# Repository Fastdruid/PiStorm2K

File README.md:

# PiStorm2K v2.1 - BOSS Edition.

This is a rework of the original PiStorm2K to add some additional potential capabilities while remaining 100% compatible with existing and future firmware. 

The original PiStorm2K was imported from Gerbers into KiCAD and then revised. The initial KiCAD PiStorm2K is also contained within this repo however there were a lots of bits cleaned-up on v2.0 that didn't happen on v1.0. 

# Why

An excellent question. I don't even have an Amiga 2000 (any donations of one welcome however!)
This all spiralled from LazaruStorm not playing nicely with the original Processor on my 68k. This took me down the hole of *why* it didn't, because it _should_. In short the issue is due to the E(nable) Clock that is used for 6800 type devices (which the CIA chips are). The 68k does not stop generating the E-Clock, there is no way to tell at what state it will start up in and so it's a random lottery if the E-Clock generated from the PiStorm happens to "line up". 

I then took a look at the Verilog firmware and thought "this appears reasonably understandable". From there I got the PiStorm to start off by listening for the E-Clock, and either generate one or sync to an existing one. After that I got it to correctly Bus Arbitrate and request the Bus rather than the brute force method LazaruStorm uses of just holding BR asserted. 

Once I'd got that working nicely I then got it to swap between PiStorm and original processor using a long hold Ctrl-A-A. 

At the same time I looked at the Zorro-II specs pinout for the Denise I'd just built and realised it was 98% compatible with the A2000 Co-Processor, had no 7MHz clock on pin 7 but could do the same as the A2000 and generate it from C1/C3.
I ordered one of those and created an adaptor to fit it into the Zorro-II slot and re-wrote the firmware to swap between modes on the CLK_SEL pin (because Denise can't do a long Ctrl-A-A but has a mechanism to disable items via numlock->reset).

I also designed an adaptor to fit the card inside the A500(+). By this stage I was experimenting with a bunch of stuff and wanted something where I could access the remaining lines on the CPLD and at the same time be a useful upgrade. Which is where this comes in.
With appropriate firmware it should be able to do the same in a B2000 as it does in the A500(+) and Denise. ie swap between 68k and PiStorm at will. In theory the firmware may also do DMA...but that is very, very untested. 

# Status
V2.0 not recommended for production. 
V2.1 Fixed issues with v2.0

# Building 
## Options
   1) U6 & C13 are optional. Not so much use on the A2000, desired for the B2000
   2) H1, H2 and H3 are optional as they can be controlled by solder blobs however H4 is required. 
   3) R3 is optional and for 99.9% of use cases is pointless. 
   4) For A2000 R4 can be omitted. 

## Known issues
 1) V2.0 of the BOM incorrectly used 0603 for the resistors and capacitors where the footprint was 0402. Fixed in BOM v2.0.1
 2) V2.0 of the BOM incorrectly used a 680R resistor instead of a 68R for R3. Fixed in BOM v2.0.1
 3) V2.0 of the BOM incorrectly used a 1K1 resistor instead of a 1K for R3. Fixed in BOM v2.0.1
 4) Rotations of the chips are all wrong from the placement file. I need to understand here why KiCAD messed it up but if ordering from JLCPCB you will need to manually rotate them to the correct orientation.
 5) V2.0 Rogue via missed in DRC shorts 5v to GND. Can be drilled out but will be fixed in V2.1

# Summary of changes
### Additional control lines.

INT2 => Pin 87  
CFGOUTn => Pin 92  
INT6 => Pin 1  
XRDY => Pin 95  
OVR => Pin 11  

### Additional Headers / Jumpers

INT PWR => INTernal PoWeR - Optional to power the RPi from the board or use a seperate Power Supply.   
EXT => Extra - For future expansion  
E RES => This is a bit of a specialist one, this edition can be used in a normal Zorro slot with some modifications. Depending on board you may need to add a 68R resistor to the E-Clock. This jumper **BYPASSES** it. A/B2000 users should either have a jumper or solder the blob.   
CLK SEL => CLocK SELect - Close to use C1/C3 for the clock. Note that the 7MHz clock is *ALWAYS* recommended over the C1/C3 if you have it.   
BJ => Pull down BOSS (pin 20) to GND to take over from the onboard processor.   
JTAG => TDI, TCK, TMS, TDO header (see section on JTAG).   
PWR => +5V, GND, VCC_INT and VCC. Normally VCC and VCC_INT will be identical at 3.3v however if MAX V is used with the second 1.8v regulator VCC_INT will be 1.8v.   
IPL2-0 => IPL2, IPL1, IPL0. - Another specialist one. (see "use in Zorro-II slots")  

### Solder blob jumpers

SJ1 - Close to use C1/C3 - semi-permanent version of **CLK SEL** Jumper. A2000 users should close this. B2000 should leave it open.   
SJ2 - Close to bypass 68R on E-Clock - semi-permanent version of **E RES** Jumper. A2000 and B2000 users should close this.  
BOSS - Close to pull BOSS down to GND - semi-permanent version of BOSS Jumper.  
D-BOSS - Cut to disable pin 20 (see "use in Zorro slot").  
TDI => Cut pin 1-2 to disable TDI to the CPLD. Close 2-3 to redirect RPi Pin 13 (GPIO27) to Pin 89 on the CPLD.  
TMS => Cut pin 1-2 to disable TMS to the CPLD. Close 2-3 to redirect RPi Pin 18 (GPIO24) to Pin 91 on the CPLD.  
TDO => Cut pin 1-2 to disable TDO to the CPLD. Close 2-3 to redirect RPi Pin 22 (GPIO25) to Pin 85 on the CPLD.  
TCK => Cut pin 1-2 to disable TCK to the CPLD. Close 2-3 to redirect RPi Pin 37 (GPIO26) to Pin 86 on the CPLD.  
7MHz => Cut to disconnect pin 7 (see "use in Zorro-II slots").  

### Extra pins
The remaining 4 extra pins are brought out to solder pads.   
P78 - Pin 78 CPLD  
P81 - Pin 81 CPLD  
P82 - Pin 82 CPLD  
P83 - Pin 83 CPLD  

# Use in Zorro-II slots. 

This can be used in an unbuffered Zorro-II slot noting a couple of potential issues.  

1) Zorro is a 100 pin slot, the Co-Processor is 86. It *must* be fitted so pin 1 is at pin 1. That means that there should be a space at the "front" of the Amiga. 
2) Pin 20 on Zorro-II is -12v. If you plug this straight in you will fry the CPLD. Cut the D-BOSS solder jumper and ensure there is no continuity across it.
3) There is no clock on pin 7. Depending on Zorro implementation this may be /OWN. If this is the case then it can be disconnected by cutting the solder blob link marked 7MHz.
4) Depending on Zorro implentation there may be no IPL0-2 lines. These are essential and therefore a header is supplied.
5) Depending on Zorro implementation there may or may not be a 68R between the Zorro slot and the CIA chips. This probably isn't a *massive* issue (after all the early A500's didn't) but a jumper is supplied just in case.

# JTAG programming.

The original PiStorm uses 4 pins from the Pi to allow quick and easy reprogramming of the CPLD. This has numerous advantages however it leaves 4 GPIO pins "off the table" that could be used. Nothing *currently* uses them however the PiStorm32 uses pins 13, 18, 22 and 37 connected to pins 31, 28,  4 &  33 which are used as PI_A[0], PI_A[1], PI_WR and PI_SER_CLK.
In theory these could be used however it makes programming a manual job to connect up a programmer. To make it slightly easier there is a 4-pin header which have the 4 pins required to flash the CPLD from the Pi using the normal procedure. 

If you wish to program the CPLD via this method use the following pinout to connect the Pi to the JTAG connector as follows.

<IMG SRC="https://www.raspberrypi.com/documentation/computers/images/GPIO-Pinout-Diagram-2.png">

Pin 13 on the Pi to TDI  (Pin 1, top of the board)  
Pin 37 on the Pi to TCK  (Pin 2)  
Pin 18 on the Pi to TMS  (Pin 3)  
Pin 22 on the Pi to TDO  (Pin 4)  

You will also need to connect power and ground to the Pi. To aid in this there is a second header next to the JTAG header marked PWR, connect power as follows.
Pin 1 or 2 on the Pi to +5V (Pin 1, top of the board).  
Pin 6,9,14,20,25,30,34 or 39 on the Pi to GND (Pin 2).  

I strongly recommend that you connect these with power off! You can then turn on your Amiga (ensuring the Pi cannot short on anything) which will boot the Pi and then allow you to flash as normal. 

Alternatively you can remove the PiStorm2k from the Amiga and provide power to the Pi via the USB power connector. This will then provide enough power back to the PiStorm2K to flash. 

# New Firmware!

This is the juicy part. There is new exciting firmware which attempts both to properly negotiate BOSS and maybe even allow Bus Arbitration which will (maybe) allow DMA. See the firmware folder for further details (if there isn't one then nothing is yet released).

# DISCLAIMER / LICENSE

Both the original PiStorm and this modification fall under the MIT License. 

THIS DESIGN, ANY HARDWARE PRODUCED FROM IT, ANY FIRMWARE OR SOFTWARE IS PROVIDED "AS IS" WITHOUT WARRANTY OF ANY KIND, EXPRESS OR IMPLIED, INCLUDING BUT NOT LIMITED TO THE WARRANTIES OF MERCHANTABILITY, FITNESS FOR A PARTICULAR PURPOSE AND NONINFRINGEMENT. IN NO EVENT SHALL THE AUTHORS OR COPYRIGHT HOLDERS BE LIABLE FOR ANY CLAIM, DAMAGES OR OTHER LIABILITY, WHETHER IN AN ACTION OF CONTRACT, TORT OR OTHERWISE, ARISING FROM, OUT OF OR IN CONNECTION WITH THE DESIGN, SOFTWARE, HARDWARE, FIRMWARE OR THE USE OR OTHER DEALINGS IN THE DESIGN, SOFTWARE, HARDWARE or FIRMWARE.

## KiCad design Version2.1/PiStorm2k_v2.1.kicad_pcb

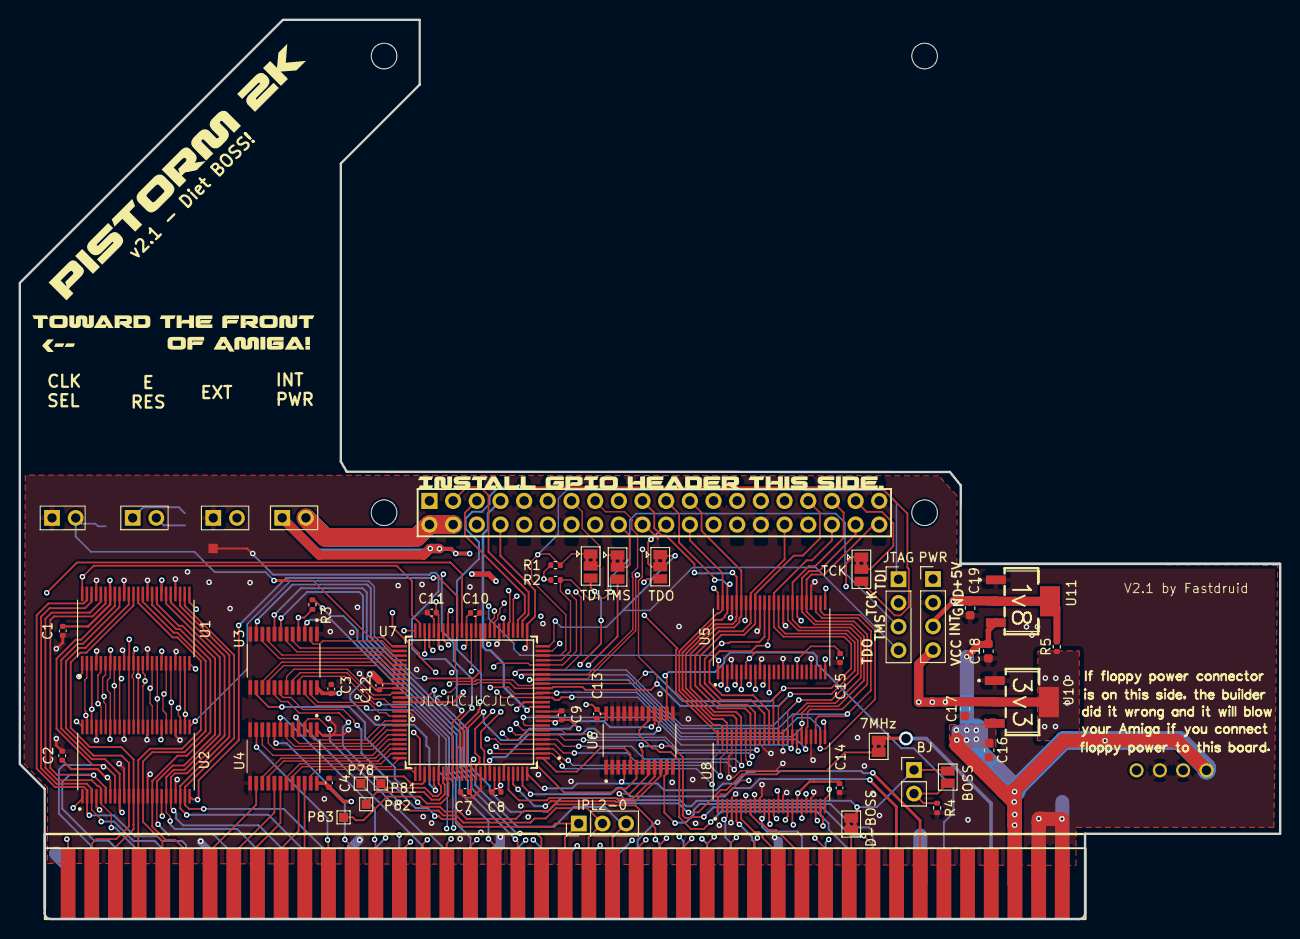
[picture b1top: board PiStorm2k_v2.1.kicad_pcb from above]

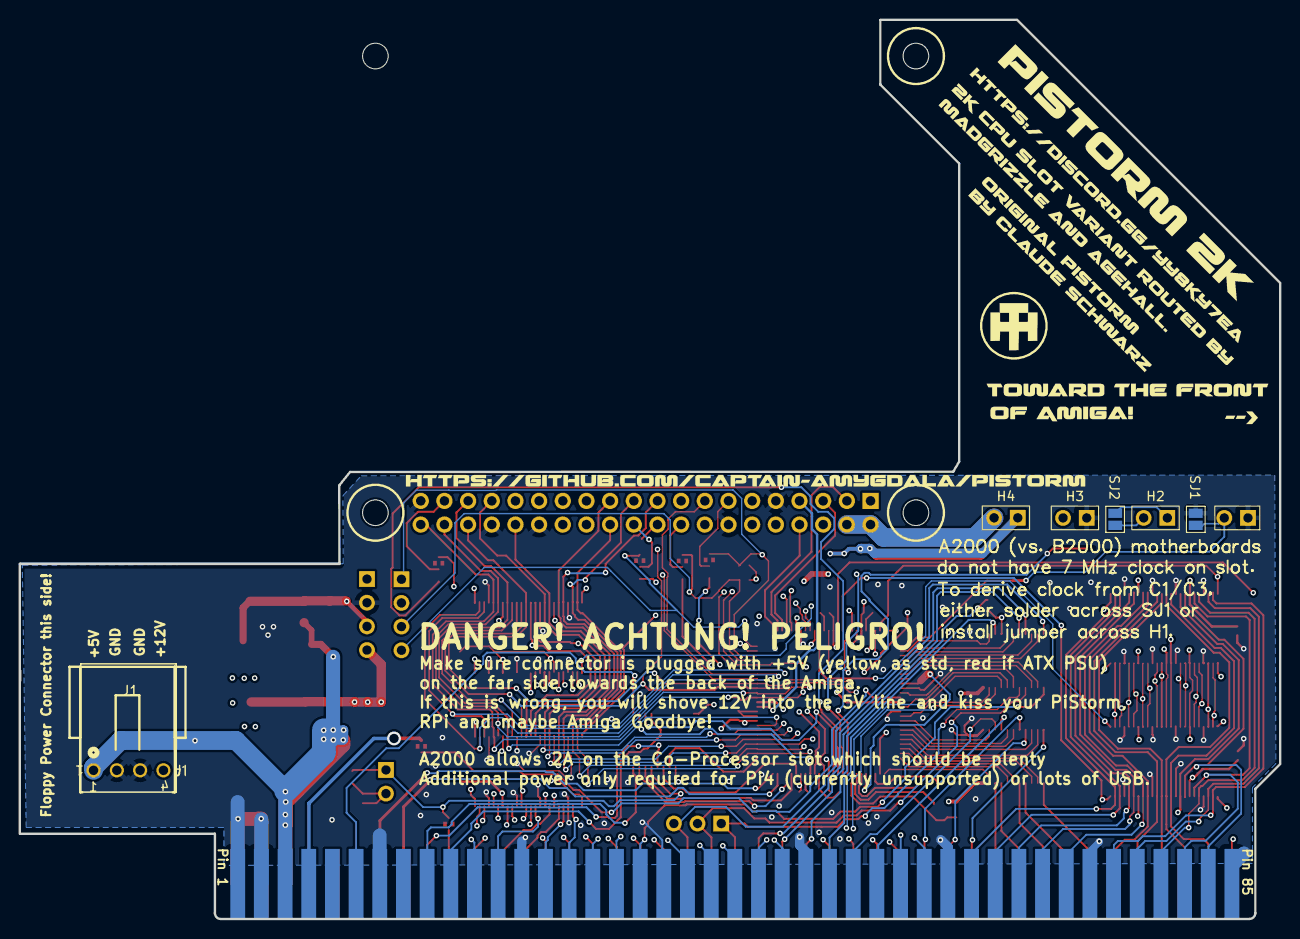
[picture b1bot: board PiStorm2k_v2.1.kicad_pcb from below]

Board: 4 copper layers, 135.2 x 96.5 mm, 56 parts (3 on the bottom side), 158 nets.

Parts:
7MHz: SolderJumper-2_P1.3mm_Bridged2Bar_Pad1.0x1.5mm
BJ: PinHeader_1x02_P2.54mm_Vertical
BOSS: SolderJumper-2_P1.3mm_Open_Pad1.0x1.5mm
C1, C2, C3, C4, C7, C8, C9, C10, C11, C12, C13, C14, C15: 100nf; C_0402_1005Metric
C16, C17, C18, C19: C_0603_1608Metric
D-BOSS: SolderJumper-2_P1.3mm_Bridged2Bar_Pad1.0x1.5mm
H1, H2, H3, H4: PinHeader_1x02_P2.54mm_Horizontal
IPL2-0: PinHeader_1x03_P2.54mm_Vertical
J1: CONN_171826-4_TYCO_TYC
JTAG: PinHeader_1x04_P2.54mm_Vertical
P78, P81, P82, P83: TestPoint_Pad_1.0x1.0mm
PWR: PinHeader_1x04_P2.54mm_Vertical
R1, R2, R3, R4, R5: R_0402_1005Metric
RPi: Raspberry_Pi_2_3; raspberrypi_2_3
SJ1, SJ2: SolderJumper-2_P1.3mm_Open_Pad1.0x1.5mm
TCK: SolderJumper-3_P1.3mm_Bridged2Bar12_Pad1.0x1.5mm
TDI: SolderJumper-3_P1.3mm_Bridged2Bar12_Pad1.0x1.5mm
TDO: SolderJumper-3_P1.3mm_Bridged2Bar12_Pad1.0x1.5mm
TMS: SolderJumper-3_P1.3mm_Bridged2Bar12_Pad1.0x1.5mm
U1, U2, U5, U8: SN74LVC16374DGGR; SOP50P810X120-48N
U3, U4, U6: SN74CBTD3384PWR; SOP65P640X120-24N
U7: QFP50P1600X1600X120-100N
U10, U11: VREG_LM1117IMPX-3.3
Zorro II / A(B) Co-Processor: zorro2port; A500_Edge

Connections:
1_CPLD: U6.5, U7.1
4_E: H2.1, R3.1, SJ2.2, U3.4
52_1B1: U3.2, U7.52
53_1B2: U3.5, U7.53
54_1B3: U3.6, U7.54
55_1B4: U3.9, U7.55
56_1B5: U3.10, U7.56
57_2B1: U3.15, U7.57
58_2B2: U3.16, U7.58
61_2B3: U3.19, U7.61
62_GCLK2: 7MHz.1, U7.62
64_2B4: U3.20, U7.64
66_2B5: U3.23, U7.66
67_1B1: U4.2, U7.67
68_1B2: U4.5, U7.68
69_1B1: U4.6, U7.69
70_1B4: U4.9, U7.70
71_1B5: U4.10, U7.71
72_2B1: U4.15, U7.72
73_2B2: U4.16, U7.73
74_2B3: U4.19, U7.74
75_2B4: U4.20, U7.75
76_2B5: U4.23, U7.76
78_CPLD: P78.1, U7.78
81_CPLD: P81.1, U7.81
82_CPLD: P82.1, U7.82
83_CPLD: P83.1, U7.83
85_CPLD: TDO.3, U7.85
86_CPLD: TCK.3, U7.86
87_CPLD: U6.16, U7.87
89_CPLD: TDI.3, U7.89
91_CPLD: TMS.3, U7.91
92_CPLD: U6.15, U7.92
95_1B3: U6.6, U7.95
96_1B4: U6.9, U7.96
97_1B5: U6.10, U7.97
+3.3V: RPi.1, RPi.17
+5V: C3.2, C4.1, C13.2, C16.1, C18.2, H4.1, J1.1, PWR.1, U3.24, U4.24, U6.24, U10.3, U11.3, Zorro II / A(B) Co-Processor.5, Zorro II / A(B) Co-Processor.6
+12V: J1.4, Zorro II / A(B) Co-Processor.10
A1: U8.3, Zorro II / A(B) Co-Processor.29
A2: U8.5, Zorro II / A(B) Co-Processor.27
A3: U8.6, Zorro II / A(B) Co-Processor.26
A4: U8.8, Zorro II / A(B) Co-Processor.24
A5: U8.9, Zorro II / A(B) Co-Processor.21
A6: U8.11, Zorro II / A(B) Co-Processor.23
A7: U8.12, Zorro II / A(B) Co-Processor.28
A8: U8.13, Zorro II / A(B) Co-Processor.30
A9: U8.14, Zorro II / A(B) Co-Processor.32
A10: U8.16, Zorro II / A(B) Co-Processor.34
A11: U8.17, Zorro II / A(B) Co-Processor.36
A12: U8.19, Zorro II / A(B) Co-Processor.38
A13: U8.20, Zorro II / A(B) Co-Processor.39
A14: U8.22, Zorro II / A(B) Co-Processor.41
A15: U8.23, Zorro II / A(B) Co-Processor.43
A16: U5.2, Zorro II / A(B) Co-Processor.45
A17: U5.3, Zorro II / A(B) Co-Processor.47
A18: U5.5, Zorro II / A(B) Co-Processor.52
A19: U5.6, Zorro II / A(B) Co-Processor.54
A20: U5.8, Zorro II / A(B) Co-Processor.56
A21: U5.9, Zorro II / A(B) Co-Processor.58
A22: U5.11, Zorro II / A(B) Co-Processor.57
A23: U5.12, Zorro II / A(B) Co-Processor.59
ADDR_LTCH_0: U7.44, U8.48
ADDR_LTCH_8: U7.42, U8.25
ADDR_LTCH_16: U5.48, U7.47
ADDR_LTCH_24: U5.25, U7.48
ADDR_OE: U5.1, U5.24, U7.43, U8.1, U8.24
AS: U4.14, Zorro II / A(B) Co-Processor.74
AUX0: RPi.27, U7.30
AUX1: RPi.28, U7.33
BEER: U3.8, Zorro II / A(B) Co-Processor.46
BGACK: U4.8, Zorro II / A(B) Co-Processor.62
BOSS: BJ.1, BOSS.2, D-BOSS.2, U6.8
BOSS_G: BJ.2, BOSS.1, R4.1
BOSS_PIN: D-BOSS.1, Zorro II / A(B) Co-Processor.20
CBG: U4.11, Zorro II / A(B) Co-Processor.64
CBR: U4.7, Zorro II / A(B) Co-Processor.60
CCK: U7.99, Zorro II / A(B) Co-Processor.16
CCKQ: U7.100, Zorro II / A(B) Co-Processor.14
CFGOUTn: U6.14, Zorro II / A(B) Co-Processor.11
CLK_SEL: H1.2, SJ1.1, U7.51
D0: U1.47, U2.2, Zorro II / A(B) Co-Processor.75
D1: U1.46, U2.3, Zorro II / A(B) Co-Processor.77
D2: U1.44, U2.5, Zorro II / A(B) Co-Processor.79
D3: U1.43, U2.6, Zorro II / A(B) Co-Processor.81
D4: U1.41, U2.8, Zorro II / A(B) Co-Processor.83
D5: U1.40, U2.9, Zorro II / A(B) Co-Processor.86
D6: U1.38, U2.11, Zorro II / A(B) Co-Processor.84
D7: U1.37, U2.12, Zorro II / A(B) Co-Processor.82
D8: U1.36, U2.13, Zorro II / A(B) Co-Processor.80
D9: U1.35, U2.14, Zorro II / A(B) Co-Processor.78
D10: U1.33, U2.16, Zorro II / A(B) Co-Processor.76
D11: U1.32, U2.17, Zorro II / A(B) Co-Processor.71
D12: U1.30, U2.19, Zorro II / A(B) Co-Processor.69
D13: U1.29, U2.20, Zorro II / A(B) Co-Processor.67
D14: U1.27, U2.22, Zorro II / A(B) Co-Processor.65
D15: U1.26, U2.23, Zorro II / A(B) Co-Processor.63
DATA_RD_LTCH_HB: U1.25, U7.50
DATA_RD_LTCH_LB: U1.48, U7.49
DATA_RD_OE: U1.1, U1.24, U7.38
DATA_WR_LTCH_HB: U2.25, U7.36
DATA_WR_LTCH_LB: U2.48, U7.40
DATA_WR_OE: U2.1, U2.24, U7.41
DTACK: U4.22, Zorro II / A(B) Co-Processor.66
E: H2.2, R3.2, SJ2.1, Zorro II / A(B) Co-Processor.50
EXTRA: H3.2, U7.77
FC0: U3.22, Zorro II / A(B) Co-Processor.31
FC1: U3.21, Zorro II / A(B) Co-Processor.33
FC2: U3.14, Zorro II / A(B) Co-Processor.35
GND: C1.1, C2.2, C4.2, C7.2, C8.1, C9.2, C10.2, C11.2, C12.2, C13.1, C14.2, C15.2, C16.2, C17.1, C18.1, C19.1, H1.1, H3.1, J1.2, J1.3, PWR.2, R4.2, RPi.6, RPi.9, RPi.14, RPi.20, RPi.25, RPi.30, RPi.34, RPi.39, SJ1.2, U1.4, U1.10, U1.15, U1.21, U1.28, U1.34, U1.39, U1.45, U2.4, U2.10, U2.15, U2.21, U2.28, U2.34, U2.39, U2.45, U3.1, U3.12, U3.13, U4.1, U4.12, U4.13, U5.4, U5.10, U5.15, U5.21, U5.28, U5.34, U5.39, U5.45, U6.1, U6.2, U6.3, U6.12, U6.13, U6.18, U6.19, U6.20, U6.21, U6.22, U6.23, U7.10, U7.11, U7.32, U7.37, U7.46, U7.60, U7.65, U7.79, U7.90, U7.93, U8.4, U8.10, U8.15, U8.21, U8.28, U8.34, U8.39, U8.45, U10.1, U11.1, Zorro II / A(B) Co-Processor.1, Zorro II / A(B) Co-Processor.2, Zorro II / A(B) Co-Processor.3, Zorro II / A(B) Co-Processor.4, Zorro II / A(B) Co-Processor.13, Zorro II / A(B) Co-Processor.25, Zorro II / A(B) Co-Processor.37, Zorro II / A(B) Co-Processor.49, Zorro II / A(B) Co-Processor.61, Zorro II / A(B) Co-Processor.73, Zorro II / A(B) Co-Processor.85
HLT: U4.4, Zorro II / A(B) Co-Processor.55
INT2: U6.17, Zorro II / A(B) Co-Processor.19
INT6: U6.4, Zorro II / A(B) Co-Processor.22
IPL0: IPL2-0.3, U3.11, Zorro II / A(B) Co-Processor.40
IPL1: IPL2-0.2, U3.17, Zorro II / A(B) Co-Processor.42
IPL2: IPL2-0.1, U3.18, Zorro II / A(B) Co-Processor.44
LDS: U4.18, Zorro II / A(B) Co-Processor.70
OVR: U6.11, Zorro II / A(B) Co-Processor.17
PICLK: RPi.7, U7.12
PI_+5V: H4.2, RPi.2, RPi.4
RST: U4.3, Zorro II / A(B) Co-Processor.53
R_W: U4.21, Zorro II / A(B) Co-Processor.68
SA0: RPi.29, U7.34
SA1: RPi.5, U7.28
SA2: RPi.3, U7.27
SD0: RPi.24, U1.2, U2.47, U5.47, U7.2, U8.47
SD1: RPi.21, U1.3, U2.46, U5.46, U7.3, U8.46
SD2: RPi.19, U1.5, U2.44, U5.44, U7.4, U8.44
SD3: RPi.23, U1.6, U2.43, U5.43, U7.5, U8.43
SD4: RPi.32, U1.8, U2.41, U5.41, U7.6, U8.41
SD5: RPi.33, U1.9, U2.40, U5.40, U7.7, U8.40
SD6: RPi.8, U1.11, U2.38, U5.38, U7.26, U8.38
SD7: RPi.10, U1.12, U2.37, U5.37, U7.21, U8.37
SD8: RPi.36, U1.13, U2.36, U5.36, U7.17, U8.36
SD9: RPi.11, U1.14, U2.35, U5.35, U7.16, U8.35
SD10: RPi.12, U1.16, U2.33, U5.33, U7.20, U8.33
SD11: RPi.35, U1.17, U2.32, U5.32, U7.8, U8.32
SD12: RPi.38, U1.19, U2.30, U5.30, U7.15, U8.30
SD13: RPi.40, U1.20, U2.29, U5.29, U7.14, U8.29
SD14: RPi.15, U1.22, U2.27, U5.27, U7.19, U8.27
SD15: RPi.16, U1.23, U2.26, U5.26, U7.18, U8.26
SOE: RPi.31, U7.35
SWE: RPi.26, U7.29
TCK: JTAG.2, TCK.1, U7.24
TCK_PIN: RPi.37, TCK.2
TDI: JTAG.1, R1.2, TDI.1, U7.23
TDI_PIN: RPi.13, TDI.2
TDO: JTAG.4, TDO.1, U7.25
TDO_PIN: RPi.22, TDO.2
TMS: JTAG.3, R2.2, TMS.1, U7.22
TMS_PIN: RPi.18, TMS.2
UDS: U4.17, Zorro II / A(B) Co-Processor.72
V7M: 7MHz.2, Zorro II / A(B) Co-Processor.7
VCC: C1.2, C2.1, C8.2, C9.1, C11.1, C12.1, C14.1, C15.1, C17.2, PWR.4, R1.1, R2.1, R5.1, U1.7, U1.18, U1.31, U1.42, U2.7, U2.18, U2.31, U2.42, U5.7, U5.18, U5.31, U5.42, U7.9, U7.31, U7.45, U7.59, U7.80, U7.94, U8.7, U8.18, U8.31, U8.42, U10.2, U10.4
VCC_INT: C7.1, C10.1, C19.2, PWR.3, R5.2, U7.13, U7.39, U7.63, U7.88, U11.2, U11.4
VMA: U3.3, Zorro II / A(B) Co-Processor.51
VPA: U3.7, Zorro II / A(B) Co-Processor.48
XRDY: U6.7, Zorro II / A(B) Co-Processor.18

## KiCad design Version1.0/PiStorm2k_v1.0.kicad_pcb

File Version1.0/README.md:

This is the original PiStorm2K converted from Gerbers to KiCAD and appropriate footprints applied.

There were a *LOT* of changes made in v2.0 that are not reflected back in v1.0, this version is not suitable for production as it currently stands. 

Most of the issues are because it was imported from Gerbers all of the pads/paste/solder masks are individual items not footprints. I cleaned up some but even when putting V2.0 into order I spotted I'd missed some! 
It's probably not *as* critical with v1.0 as nothing moved but be aware of it. 

USE AT YOUR OWN RISK.

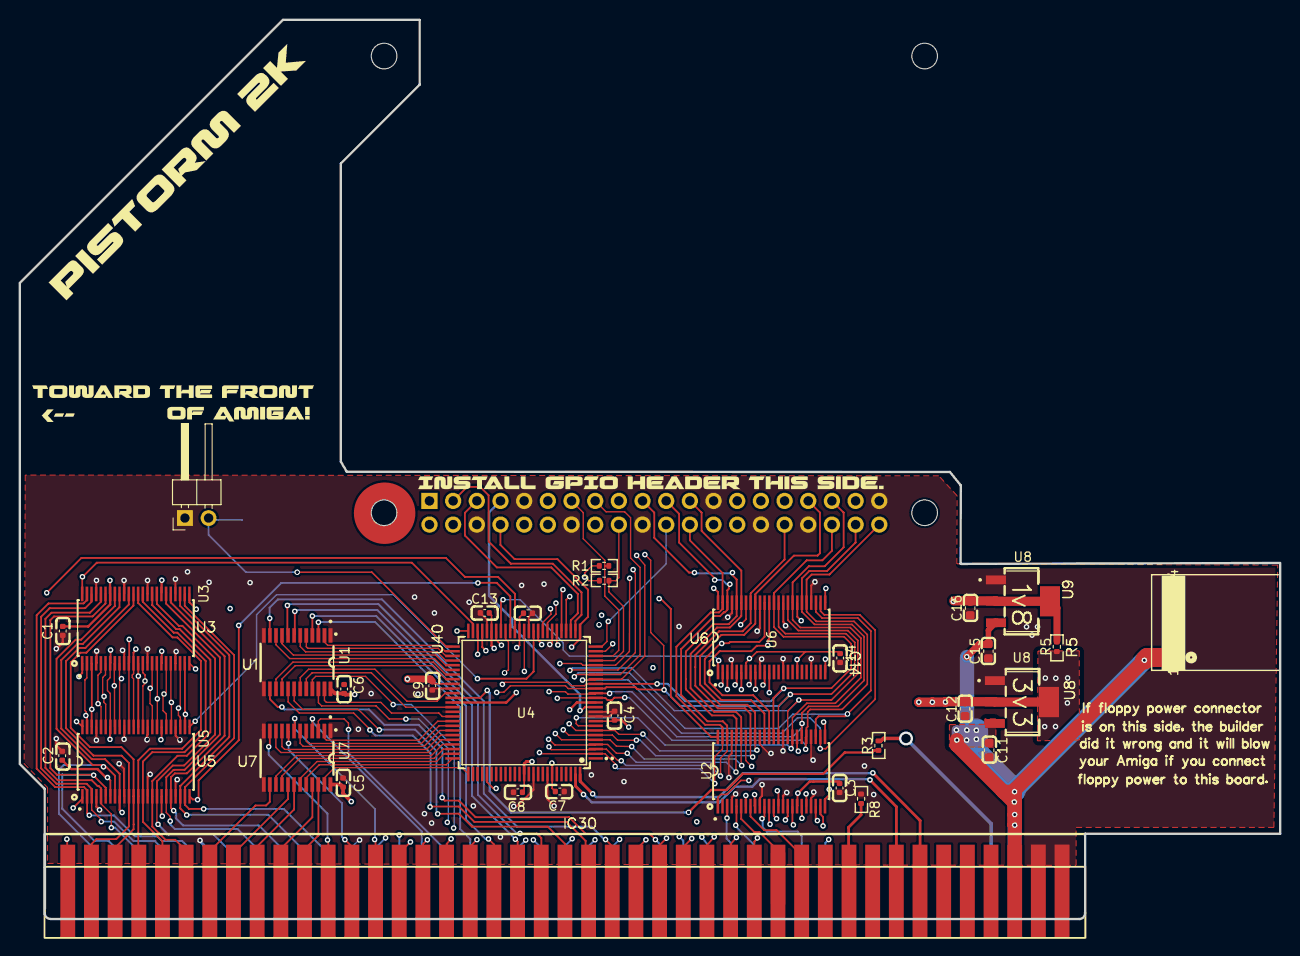
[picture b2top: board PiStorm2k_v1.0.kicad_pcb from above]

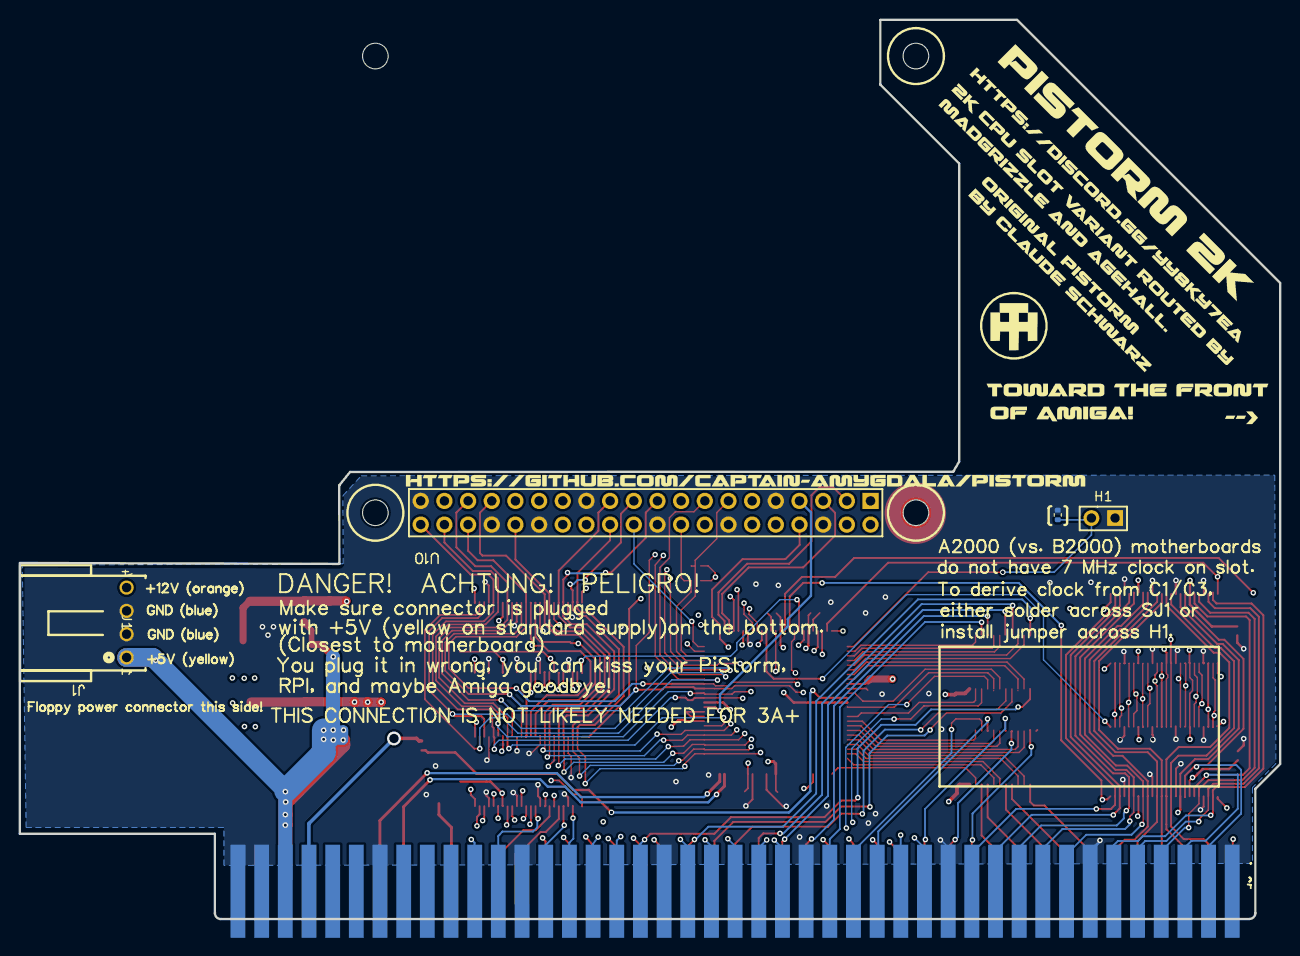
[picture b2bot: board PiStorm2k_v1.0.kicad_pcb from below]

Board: 4 copper layers, 135.2 x 96.5 mm, 35 parts (2 on the bottom side), 130 nets.

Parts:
C1, C2, C3, C4, C5, C6, C7, C8, C9, C10, C13, C14: 100nf; C_0402_1005Metric
C11, C12, C15, C16: C_0603_1608Metric
H1: PinHeader_1x02_P2.54mm_Horizontal
J1: CONN_171826-4_TYCO_TYC
R1, R2, R3, R5, R8: R_0402_1005Metric
RP?: Raspberry_Pi_2_3; raspberrypi_2_3
SJ1: R_0402_1005Metric
U1, U7: SOP65P640X120-24N
U2, U3, U5, U6: SOP50P810X120-48N
U4: QFP50P1600X1600X120-100N
U8, U8#2: VREG_LM1117IMPX-3.3
Zorro II / A(B) Co-Processor: zorro2port; A500_Edge

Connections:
52_1B1: U1.2, U4.52
53_1B2: U1.5, U4.53
54_1B3: U1.6, U4.54
55_1B4: U1.9, U4.55
56_1B5: U1.10, U4.56
57_2B1: U1.15, U4.57
58_2B2: U1.16, U4.58
61_2B3: U1.19, U4.61
62_GCLK2: R3.1, U4.62
64_2B4: U1.20, U4.64
66_2B5: U1.23, U4.66
67_1B1: U4.67, U7.2
68_1B2: U4.68, U7.5
69_1B1: U4.69, U7.6
70_1B4: U4.70, U7.9
71_1B5: U4.71, U7.10
72_2B1: U4.72, U7.15
73_2B2: U4.73, U7.16
74_2B3: U4.74, U7.19
75_2B4: U4.75, U7.20
76_2B5: U4.76, U7.23
+3.3V: RP?.1, RP?.17
+5V: C5.1, C6.2, C11.1, C15.2, J1.1, RP?.2, RP?.4, U1.24, U7.24, U8.3, U8#2.3, Zorro II / A(B) Co-Processor.5, Zorro II / A(B) Co-Processor.6
+12V: J1.4, Zorro II / A(B) Co-Processor.10
A1: U2.3, Zorro II / A(B) Co-Processor.29
A2: U2.5, Zorro II / A(B) Co-Processor.27
A3: U2.6, Zorro II / A(B) Co-Processor.26
A4: U2.8, Zorro II / A(B) Co-Processor.24
A5: U2.9, Zorro II / A(B) Co-Processor.21
A6: U2.11, Zorro II / A(B) Co-Processor.23
A7: U2.12, Zorro II / A(B) Co-Processor.28
A8: U2.13, Zorro II / A(B) Co-Processor.30
A9: U2.14, Zorro II / A(B) Co-Processor.32
A10: U2.16, Zorro II / A(B) Co-Processor.34
A11: U2.17, Zorro II / A(B) Co-Processor.36
A12: U2.19, Zorro II / A(B) Co-Processor.38
A13: U2.20, Zorro II / A(B) Co-Processor.39
A14: U2.22, Zorro II / A(B) Co-Processor.41
A15: U2.23, Zorro II / A(B) Co-Processor.43
A16: U6.2, Zorro II / A(B) Co-Processor.45
A17: U6.3, Zorro II / A(B) Co-Processor.47
A18: U6.5, Zorro II / A(B) Co-Processor.52
A19: U6.6, Zorro II / A(B) Co-Processor.54
A20: U6.8, Zorro II / A(B) Co-Processor.56
A21: U6.9, Zorro II / A(B) Co-Processor.58
A22: U6.11, Zorro II / A(B) Co-Processor.57
A23: U6.12, Zorro II / A(B) Co-Processor.59
ADDR_LTCH_0: U2.48, U4.44
ADDR_LTCH_8: U2.25, U4.42
ADDR_LTCH_16: U4.47, U6.48
ADDR_LTCH_24: U4.48, U6.25
ADDR_OE: U2.1, U2.24, U4.43, U6.1, U6.24
AS: U7.14, Zorro II / A(B) Co-Processor.74
AUX0: RP?.27, U4.30
AUX1: RP?.28, U4.33
BEER: U1.8, Zorro II / A(B) Co-Processor.46
BGACK: U7.8, Zorro II / A(B) Co-Processor.62
BOSS: R8.1, Zorro II / A(B) Co-Processor.20
CBG: U7.11, Zorro II / A(B) Co-Processor.64
CBR: U7.7, Zorro II / A(B) Co-Processor.60
CCK: U4.99, Zorro II / A(B) Co-Processor.16
CCKQ: U4.100, Zorro II / A(B) Co-Processor.14
CLK_SEL: H1.2, SJ1.1, U4.51
D0: U3.47, U5.2, Zorro II / A(B) Co-Processor.75
D1: U3.46, U5.3, Zorro II / A(B) Co-Processor.77
D2: U3.44, U5.5, Zorro II / A(B) Co-Processor.79
D3: U3.43, U5.6, Zorro II / A(B) Co-Processor.81
D4: U3.41, U5.8, Zorro II / A(B) Co-Processor.83
D5: U3.40, U5.9, Zorro II / A(B) Co-Processor.86
D6: U3.38, U5.11, Zorro II / A(B) Co-Processor.84
D7: U3.37, U5.12, Zorro II / A(B) Co-Processor.82
D8: U3.36, U5.13, Zorro II / A(B) Co-Processor.80
D9: U3.35, U5.14, Zorro II / A(B) Co-Processor.78
D10: U3.33, U5.16, Zorro II / A(B) Co-Processor.76
D11: U3.32, U5.17, Zorro II / A(B) Co-Processor.71
D12: U3.30, U5.19, Zorro II / A(B) Co-Processor.69
D13: U3.29, U5.20, Zorro II / A(B) Co-Processor.67
D14: U3.27, U5.22, Zorro II / A(B) Co-Processor.65
D15: U3.26, U5.23, Zorro II / A(B) Co-Processor.63
DATA_RD_LTCH_HB: U3.25, U4.50
DATA_RD_LTCH_LB: U3.48, U4.49
DATA_RD_OE: U3.1, U3.24, U4.38
DATA_WR_LTCH_HB: U4.36, U5.25
DATA_WR_LTCH_LB: U4.40, U5.48
DATA_WR_OE: U4.41, U5.1, U5.24
DTACK: U7.22, Zorro II / A(B) Co-Processor.66
E: U1.4, Zorro II / A(B) Co-Processor.50
FC0: U1.22, Zorro II / A(B) Co-Processor.31
FC1: U1.21, Zorro II / A(B) Co-Processor.33
FC2: U1.14, Zorro II / A(B) Co-Processor.35
GND: C1.1, C2.2, C3.2, C4.2, C5.2, C7.1, C8.2, C9.2, C10.2, C11.2, C12.1, C13.2, C14.2, C15.1, C16.1, H1.1, J1.2, J1.3, R8.2, RP?.6, RP?.9, RP?.14, RP?.20, RP?.25, RP?.30, RP?.34, RP?.39, SJ1.2, U1.1, U1.12, U1.13, U2.4, U2.10, U2.15, U2.21, U2.28, U2.34, U2.39, U2.45, U3.4, U3.10, U3.15, U3.21, U3.28, U3.34, U3.39, U3.45, U4.10, U4.11, U4.32, U4.37, U4.46, U4.60, U4.65, U4.79, U4.90, U4.93, U5.4, U5.10, U5.15, U5.21, U5.28, U5.34, U5.39, U5.45, U6.4, U6.10, U6.15, U6.21, U6.28, U6.34, U6.39, U6.45, U7.1, U7.12, U7.13, U8.1, U8#2.1, Zorro II / A(B) Co-Processor.1, Zorro II / A(B) Co-Processor.2, Zorro II / A(B) Co-Processor.3, Zorro II / A(B) Co-Processor.4, Zorro II / A(B) Co-Processor.13, Zorro II / A(B) Co-Processor.25, Zorro II / A(B) Co-Processor.37, Zorro II / A(B) Co-Processor.49, Zorro II / A(B) Co-Processor.61, Zorro II / A(B) Co-Processor.73, Zorro II / A(B) Co-Processor.85
HLT: U7.4, Zorro II / A(B) Co-Processor.55
IPL0: U1.11, Zorro II / A(B) Co-Processor.40
IPL1: U1.17, Zorro II / A(B) Co-Processor.42
IPL2: U1.18, Zorro II / A(B) Co-Processor.44
LDS: U7.18, Zorro II / A(B) Co-Processor.70
PICLK: RP?.7, U4.12
RST: U7.3, Zorro II / A(B) Co-Processor.53
R_W: U7.21, Zorro II / A(B) Co-Processor.68
SA0: RP?.29, U4.34
SA1: RP?.5, U4.28
SA2: RP?.3, U4.27
SD0: RP?.24, U2.47, U3.2, U4.2, U5.47, U6.47
SD1: RP?.21, U2.46, U3.3, U4.3, U5.46, U6.46
SD2: RP?.19, U2.44, U3.5, U4.4, U5.44, U6.44
SD3: RP?.23, U2.43, U3.6, U4.5, U5.43, U6.43
SD4: RP?.32, U2.41, U3.8, U4.6, U5.41, U6.41
SD5: RP?.33, U2.40, U3.9, U4.7, U5.40, U6.40
SD6: RP?.8, U2.38, U3.11, U4.26, U5.38, U6.38
SD7: RP?.10, U2.37, U3.12, U4.21, U5.37, U6.37
SD8: RP?.36, U2.36, U3.13, U4.17, U5.36, U6.36
SD9: RP?.11, U2.35, U3.14, U4.16, U5.35, U6.35
SD10: RP?.12, U2.33, U3.16, U4.20, U5.33, U6.33
SD11: RP?.35, U2.32, U3.17, U4.8, U5.32, U6.32
SD12: RP?.38, U2.30, U3.19, U4.15, U5.30, U6.30
SD13: RP?.40, U2.29, U3.20, U4.14, U5.29, U6.29
SD14: RP?.15, U2.27, U3.22, U4.19, U5.27, U6.27
SD15: RP?.16, U2.26, U3.23, U4.18, U5.26, U6.26
SOE: RP?.31, U4.35
SWE: RP?.26, U4.29
TCK: RP?.37, U4.24
TDI: R1.2, RP?.13, U4.23
TDO: RP?.22, U4.25
TMS: R2.2, RP?.18, U4.22
UDS: U7.17, Zorro II / A(B) Co-Processor.72
V7M: R3.2, Zorro II / A(B) Co-Processor.7
VCC: C1.2, C2.1, C3.1, C4.1, C7.2, C9.1, C12.2, C13.1, C14.1, R1.1, R2.1, R5.1, U2.7, U2.18, U2.31, U2.42, U3.7, U3.18, U3.31, U3.42, U4.9, U4.31, U4.45, U4.59, U4.80, U4.94, U5.7, U5.18, U5.31, U5.42, U6.7, U6.18, U6.31, U6.42, U8#2.2, U8#2.4
VCC_INT: C8.1, C10.1, C16.2, R5.2, U4.13, U4.39, U4.63, U4.88, U8.2, U8.4
VMA: U1.3, Zorro II / A(B) Co-Processor.51
VPA: U1.7, Zorro II / A(B) Co-Processor.48

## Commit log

2024-02-26 Create LICENSE
2024-02-27 Updated BOM
    Mistake in some Resistors/Capacitors were previous version size of 0603 instead of 0402.
2024-03-12 Updated to v2.1
2024-03-12 Add files via upload
    Added v2.1
2024-06-25 JLCPCB production files. This was tested on real A2000 and works ok. But the BOSS pull down resistor should be 0 Ohm or something like that.
